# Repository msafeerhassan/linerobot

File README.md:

# Line Following Robot with PID
## Project Overview

Line Following Robot with PID project uses IR Sensors, Microcontroller and Motors to follow a line path on the floor. PID is a type of error-reduction algorithm implemented in such robots to reduce their errors and improve accuracy and precision.
## Project Details
This project is built under Hack Club's Blueprint Program. Custom shape PCB is be used as chassis for the car. PCB covers all components routing alongwith components mounting and soldering. This reduces the wires and improve the project's appearance. Moreover, it reduces the weight due to separate chassis making it more efficient.
N20 Gear Motors with encoders and DRV8833 Motor Driver alongwith QTR 8 Channel IR Sensor Array and ESP32 S3 Devkit are being used. Several capacitors are added to improve the current flow. A Lithium Battery powers this whole project. ESP32 is powered by 5V which is regulated via a Buck Convertor. Motors are powered by 6V and this too is regulated through a 6V 5A Buck Converter.

### PCB:

### Schematic Diagram:

### 3D Model Images:

### Why I made this project?

This was my first ever Hardware Project involving Schematic Design and PCB. I chose this project to strengthen my knowledge and skills of using sensors, microcontrollers etc. I learnt a lot about capacitance, optimum current flow and how sensors work inside. This robot will be used to compete in Line Following Robot competitions like: https://www.dmtsnust.com/nerc/. This project, though difficult but still made me believe that I can build efficient and great Hardware Projects too.

### How it will work
Firstly, battery powers everything and voltage is regulated via Buck Convertors. 
Then the IR Sensor Array gives readings to the ESP32 and based on that, ESP32 alters the speed of motors via Motor Driver.
This allows Robot to stay on line.
When PID is implemented, after this step the ESP32 counts error Value and based on that some manual variables are adjusted that results in increased accuracy and precision.
This loop continues until the robot reaches end of line and then it will stop.

### How to use it?

Firstly, order the PCB from PCB Manufacturing Service. I used JLCPCB: http://jlcpcb.com/ because they offer great and high quality services.
Then order all the components listed in the Bill of Materials.
Solder them all onto the PCB and fully assemble it.
Flash the firmware inside the ESP32. Make sure to adjust variables for better results.
BOOM!!! YOU MADE A COOL LINE FOLLOWING ROBOT.

## Bill of Materials (BOM)

| Item Name                                                   | Quantity | Link                                                                                                                              | Cost   |
|:------------------------------------------------------------|---------:|:----------------------------------------------------------------------------------------------------------------------------------|:-------|
| ESP32-DevKit-S3-WROOM1                                      |        1 | [Link](https://epro.pk/product/pre-soldered-esp32-s3-wroom-1-development-board-2-4g-wifi-bt-module/)                              | $6.41  |
| DRV8833 Motor Driver                                        |        1 | [Link](https://epro.pk/product/tb6612-drv8833-dual-motor-driver-module-1a-h-bridge-for-arduino-robotics/)                         | $1.98  |
| 6V N20 Gear Motor with encoder, wheel and mounting brackets |        2 | [Link](https://www.aliexpress.com/item/1005004110888400.html)                                                                     | $16.35 |
| 5A Buck DC-DC Converter 7.4V to 6V                          |        1 | [Link](https://www.aliexpress.com/item/4000496873234.html)                                                                        | $4.84  |
| 7.4V to 5V 1A DC-DC Fixed Buck Convertor (for ESP32)        |        1 | [Link](https://www.aliexpress.com/item/1005006005553178.html)                                                                     | $1.86  |
| 470 µF, 16 V aluminium electrolytic capacitor               |        2 | [Link](https://epro.pk/product/470uf-16v-aluminum-electrolytic-capacitor/)                                                        | $0.11  |
| 220 µF, 10 V aluminium electrolytic capacitor               |        1 | We'll buy it ourself                                                                                                              | $0.00  |
| 100 nF Ceramic Capacitor                                    |        2 | [Link](https://epro.pk/product/0-1uf-100nf-100000pf-104-ceramic-capacitor-in-pakistan/)                                           | $0.02  |
| 8 Channel IR Sensor Array                                   |        1 | [Link](https://epro.pk/product/qtr-8rc-line-following-reflectance-ir-sensor-8-channel-line-following-line-tracking-array-module/) | $2.30  |
| LiPo Battery 7.4V 1500mAH                                   |        1 | [Link](https://epro.pk/product/zop-power-7-4v-1500mah-li-po-rechargeable-battery-pack/)                                           | $10.04 |
| PCB                                                         |        1 | No Link:(                                                                                                                         | $36.25 |
| Push Switch Button                                          |        1 | [Link](https://epro.pk/product/slider-on-off-switch/)                                                                             | $0.05  |
| TAXES:(                                                     |        0 | No Link:(                                                                                                                         | $16.14 |
| Total Cost                                                  |        0 |                                                                                                                                   | $96.35 |

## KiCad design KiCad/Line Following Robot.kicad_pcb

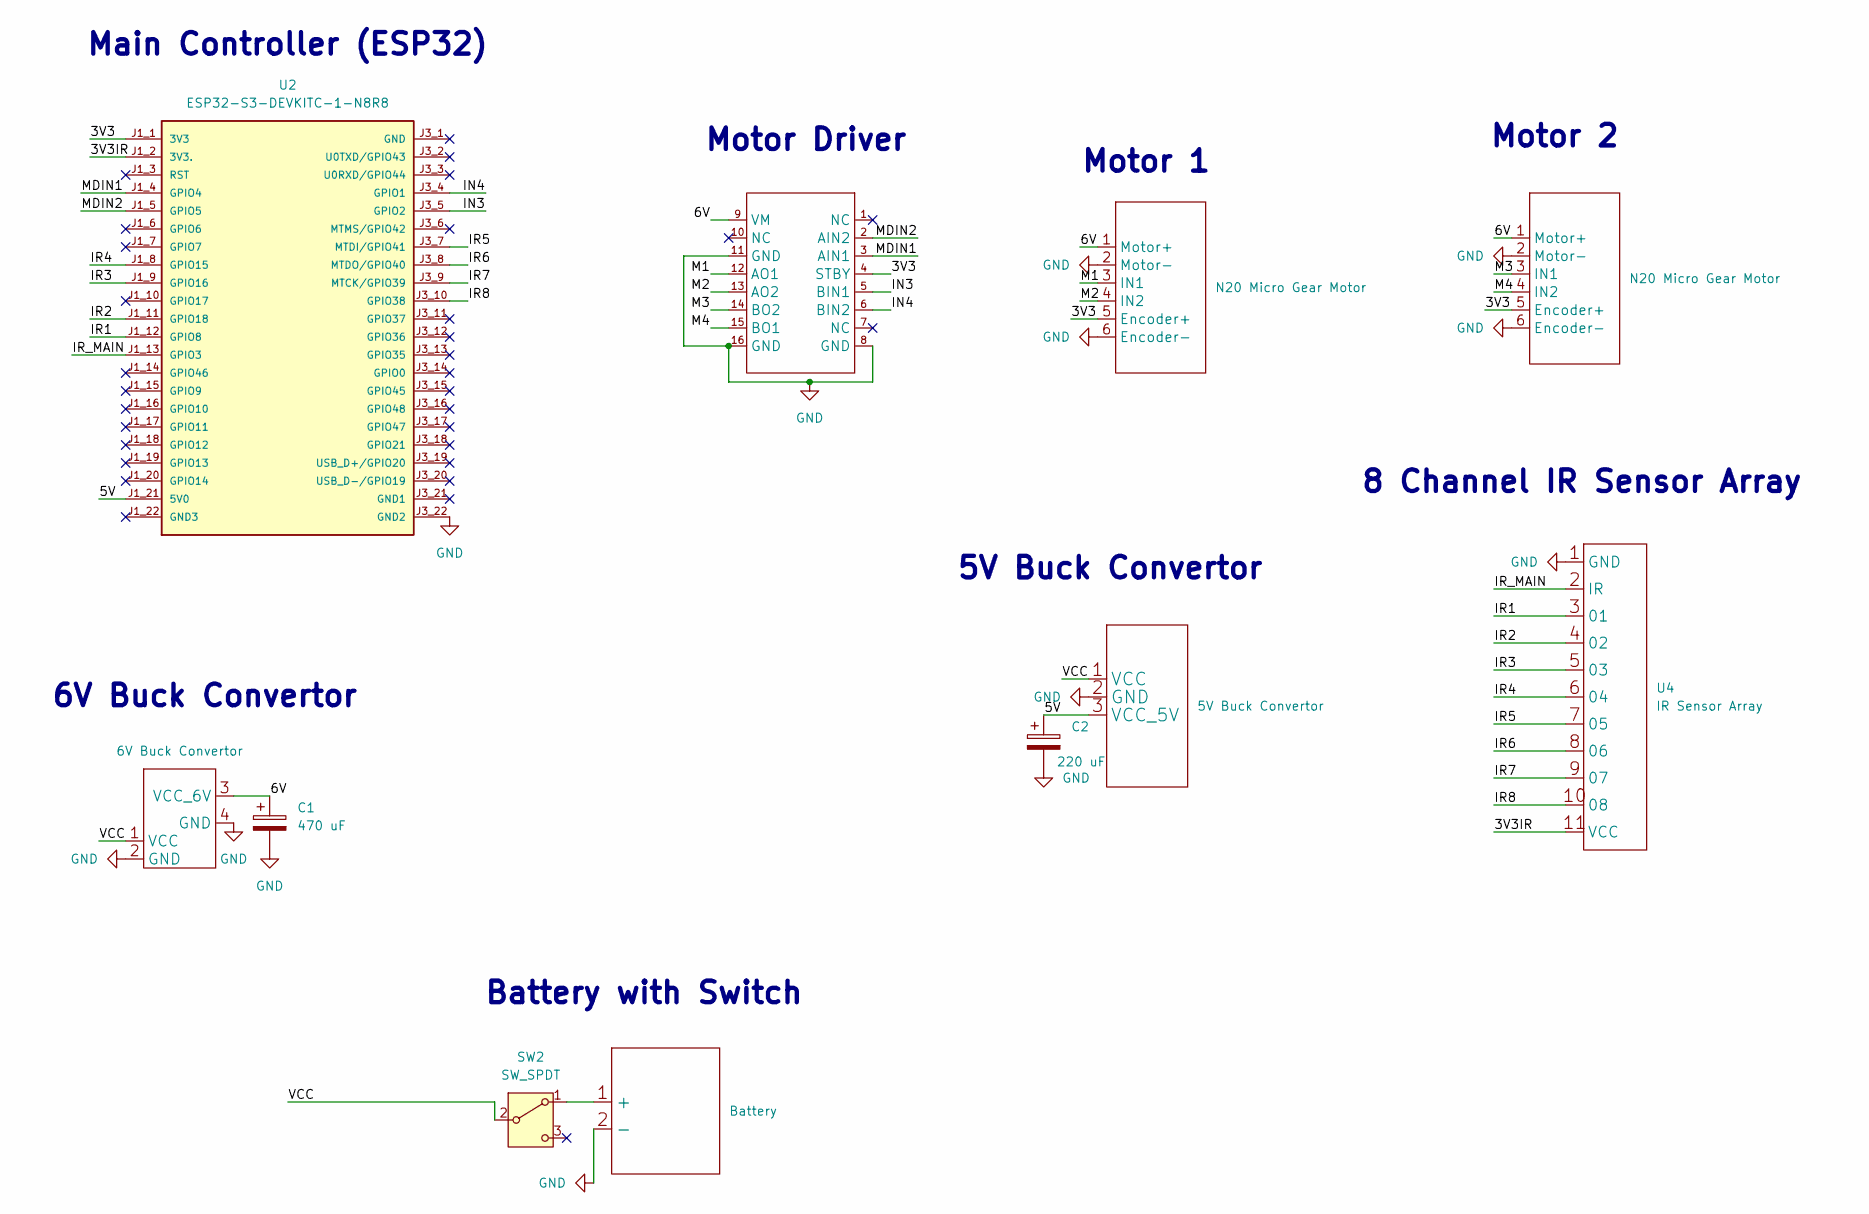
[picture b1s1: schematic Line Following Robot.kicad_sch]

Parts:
A1, A2: N20 Micro Gear Motor; Motor
C1: 470 uF; Capacitor
C2: 220 uF; Capacitor
SW2: SW_SPDT; SW_Slide-03_Wuerth-WS-SLTV_10x2.5x6.4_P2.54mm
U1: 5V Buck Convertor
U2: ESP32-S3-DEVKITC-1-N8R8
U3: 6V Buck Convertor; 6V New Buck Convertor
U4: IR Sensor Array
U6: PinHeader_1x08_P2.54mm_Vertical
U7: Battery

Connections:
/3V3: A1.5 (Encoder+), A2.5 (Encoder+), U2.J1_1 (3V3), U6.4 (STBY)
/3V3IR: U2.J1_2 (3V3.), U4.11 (VCC)
/5V: C2.1, U1.3 (VCC_5V), U2.J1_21 (5V0)
/6V: A1.1 (Motor+), A2.1 (Motor+), C1.1, U3.3 (VCC_6V), U6.9 (VM)
/IN3: U2.J3_5 (GPIO2), U6.5 (BIN1)
/IN4: U2.J3_4 (GPIO1), U6.6 (BIN2)
/IR1: U2.J1_12 (GPIO8), U4.3 (01)
/IR2: U2.J1_11 (GPIO18), U4.4 (02)
/IR3: U2.J1_9 (GPIO16), U4.5 (03)
/IR4: U2.J1_8 (GPIO15), U4.6 (04)
/IR5: U2.J3_7 (MTDI/GPIO41), U4.7 (05)
/IR6: U2.J3_8 (MTDO/GPIO40), U4.8 (06)
/IR7: U2.J3_9 (MTCK/GPIO39), U4.9 (07)
/IR8: U2.J3_10 (GPIO38), U4.10 (08)
/IR_MAIN: U2.J1_13 (GPIO3), U4.2 (IR)
/M1: A2.3 (IN1), U6.12 (AO1)
/M2: A2.4 (IN2), U6.13 (AO2)
/M3: A1.3 (IN1), U6.14 (BO2)
/M4: A1.4 (IN2), U6.15 (BO1)
/MDIN1: U2.J1_4 (GPIO4), U6.3 (AIN1)
/MDIN2: U2.J1_5 (GPIO5), U6.2 (AIN2)
/VCC: SW2.2 (B), U1.1 (VCC), U3.1 (VCC)
GND: A1.2 (Motor-), A1.6 (Encoder-), A2.2 (Motor-), A2.6 (Encoder-), C1.2, C2.2, U1.2 (GND), U2.J3_22 (GND2), U3.2 (GND), U3.4 (GND), U4.1 (GND), U6.8 (GND), U6.11 (GND), U6.16 (GND), U7.2 (-)
unnamed: SW2.1 (A), U7.1 (+)

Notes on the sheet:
6V Buck Convertor
Motor Driver
Motor 2
5V Buck Convertor
8 Channel IR Sensor Array
Main Controller (ESP32)
Battery with Switch
Motor 1

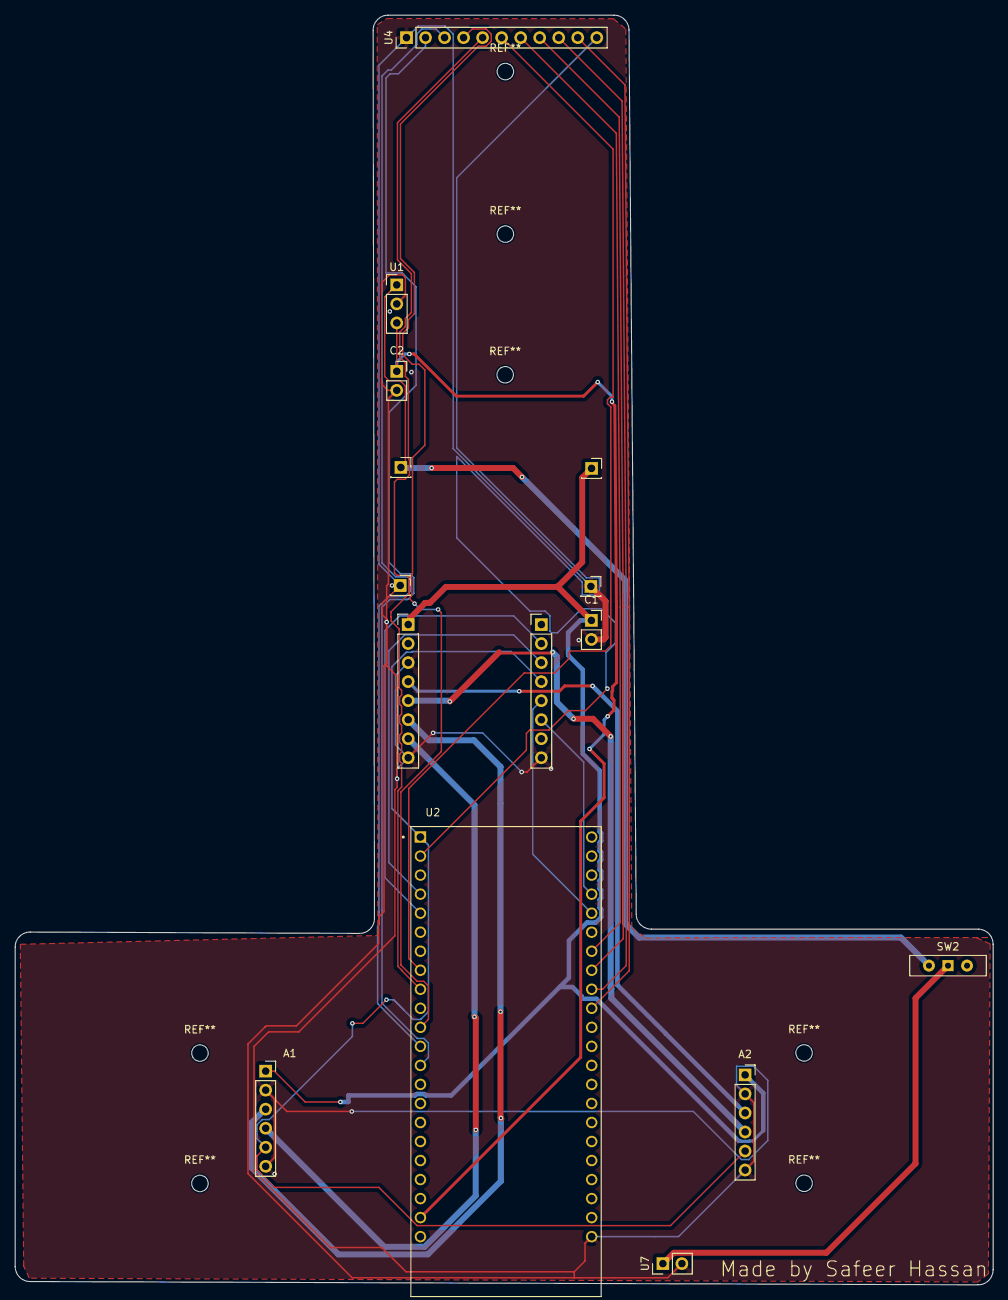
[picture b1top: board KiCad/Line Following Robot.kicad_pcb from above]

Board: 2 copper layers, 130.5 x 169.5 mm, 11 parts (0 on the bottom side), 24 nets.

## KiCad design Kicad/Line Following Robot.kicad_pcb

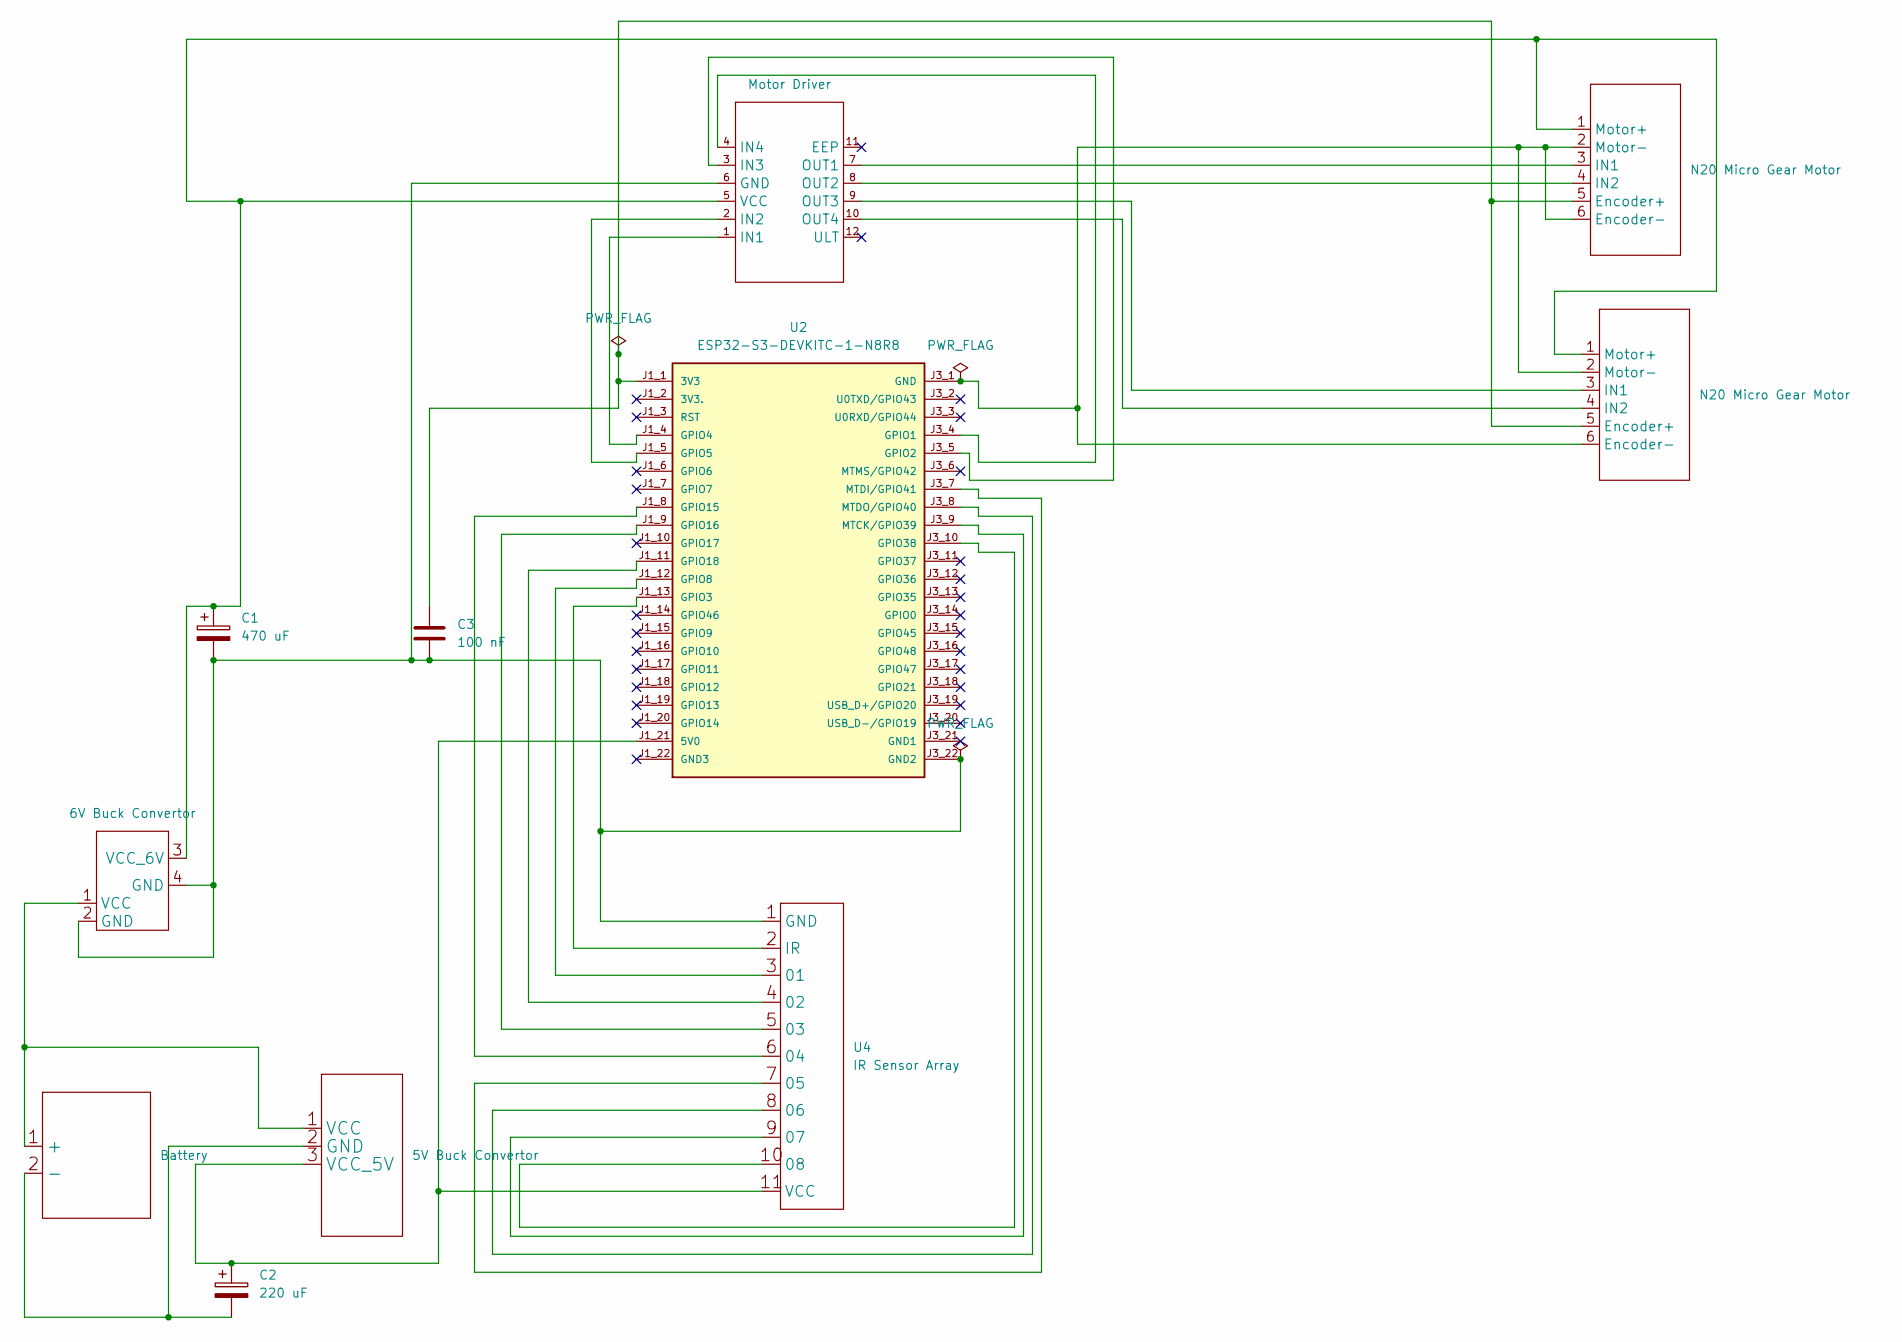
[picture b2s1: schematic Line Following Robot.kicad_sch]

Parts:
A1, A2: N20 Micro Gear Motor; Motor
C1: 470 uF; Capacitor
C2: 220 uF; Capacitor
C3: 100 nF; Capacitor
U1: 5V Buck Convertor
U2: ESP32-S3-DEVKITC-1-N8R8
U3: 6V Buck Convertor; 6V New Buck Convertor
U4: IR Sensor Array
U5: Motor Driver
U7: Battery

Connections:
unnamed: A1.5 (Encoder+), A2.5 (Encoder+), C3.1, U2.J1_1 (3V3)
unnamed: A1.2 (Motor-), A1.6 (Encoder-), A2.2 (Motor-), A2.6 (Encoder-), U2.J3_1 (GND)
unnamed: A1.3 (IN1), U5.9 (OUT3)
unnamed: A1.4 (IN2), U5.10 (OUT4)
unnamed: A1.1 (Motor+), A2.1 (Motor+), C1.1, U3.3 (VCC_6V), U5.5 (VCC)
unnamed: A2.3 (IN1), U5.7 (OUT1)
unnamed: A2.4 (IN2), U5.8 (OUT2)
unnamed: C2.2, U1.2 (GND), U7.2 (-)
unnamed: U1.1 (VCC), U3.1 (VCC), U7.1 (+)
unnamed: C2.1, U1.3 (VCC_5V), U2.J1_21 (5V0), U4.11 (VCC)
unnamed: C1.2, C3.2, U2.J3_22 (GND2), U3.2 (GND), U3.4 (GND), U4.1 (GND), U5.6 (GND)
unnamed: U2.J3_4 (GPIO1), U5.4 (IN4)
unnamed: U2.J3_5 (GPIO2), U5.3 (IN3)
unnamed: U2.J1_13 (GPIO3), U4.2 (IR)
unnamed: U2.J1_4 (GPIO4), U5.1 (IN1)
unnamed: U2.J1_5 (GPIO5), U5.2 (IN2)
unnamed: U2.J1_12 (GPIO8), U4.3 (01)
unnamed: U2.J1_8 (GPIO15), U4.6 (04)
unnamed: U2.J1_9 (GPIO16), U4.5 (03)
unnamed: U2.J1_11 (GPIO18), U4.4 (02)
unnamed: U2.J3_10 (GPIO38), U4.10 (08)
unnamed: U2.J3_9 (MTCK/GPIO39), U4.9 (07)
unnamed: U2.J3_7 (MTDI/GPIO41), U4.7 (05)
unnamed: U2.J3_8 (MTDO/GPIO40), U4.8 (06)

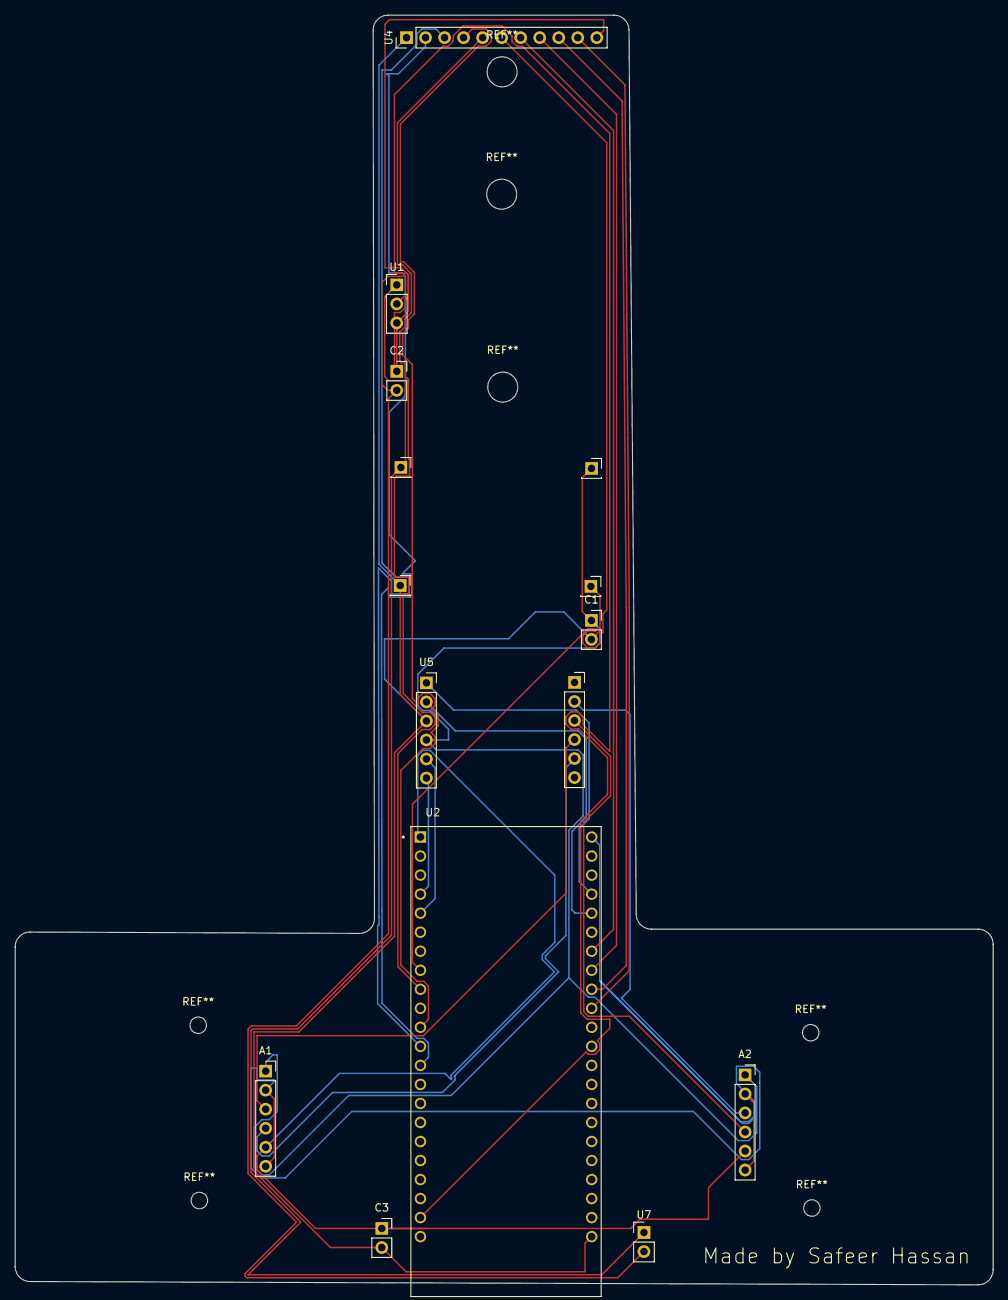
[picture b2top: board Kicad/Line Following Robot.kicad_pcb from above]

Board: 2 copper layers, 130.5 x 169.5 mm, 11 parts (0 on the bottom side), 24 nets.

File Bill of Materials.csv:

,,,,,,,,,,
,,,,Item Name,Quantity,Sourcing Link,Cost,Shipping Cost,,
,,,,ESP32 C6 DevKitM1,1,https://www.aliexpress.com/item/1005006902472832.html,$11.67 ,$3.72 ,,
,,,,DRV8833 Dual Motor Driver 1.5A,1,https://www.aliexpress.com/item/1005009787121900.html,$1.33 ,$0 ,,
,,,,6V N20 Micro Gear Motor with Encoder and Wheel,2,https://www.aliexpress.com/item/1005004110888400.html,$12.34 ,$6.15 ,,
,,,,Li-ion Battery 7.4V 2500mAH with Charger,1,https://www.aliexpress.com/item/1005009278092026.html,$21.44 ,$0 ,,
,,,,Caster Ball 22mm height,1,https://www.aliexpress.com/item/1005007433451446.html,$2.60 ,$0 ,,
,,,,5A Buck DC-DC Converter 7.4V to 6V,1,https://www.aliexpress.com/item/4000497173017.html,$5.81 ,$0 ,,
,,,,7.4V to 5V 1A DC-DC Fixed Buck Convertor (for ESP32),1,https://www.aliexpress.com/item/1005008119609403.html,$0.37 ,$3.50 ,,
,,,,"470 µF, 16 V aluminium electrolytic capacitor",10 (min. order),https://www.aliexpress.com/item/1005009114608575.html,$2.81 ,$0 ,,
,,,,"220 µF, 10 V aluminium electrolytic capacitor",10 (min. order),https://www.aliexpress.com/item/1005009114608575.html,$2.35 ,$0 ,,
,,,,"100 nF, 50 V Ceramic Capacitor",100 (min. order),https://www.aliexpress.com/item/1005007929336683.html,$0.99 ,$0 ,,
,,,,On/Off Power Switch,1,We already have this,ZERO,ZERO,,
,,,,8 Channel IR Sensor Array,1,https://www.aliexpress.com/item/1005009116199722.html,$0.86 ,$3.05 ,,
,,,,PCB,1,No Link:(,$12.40 ,$18.89 ,,
,,,,TAXES,A LOTTTT,No Link:(,$55.29 ,Not Applicable,,
,,,,Total,,$165.57 ,,,,
,,,,,,,,,,
,,,,,,,,,,
,,,,,,,,,,
,,,,,,,,,,
,,,,,,,,,,
,,,,,,,,,,
,,,,,,,,,,
,,,,,,,,,,
,,,,,,,,,,
,,,,,,,,,,
,,,,,,,,,,
,,,,,,,,,,
,,,,,,,,,,
,,,,,,,,,,
,,,,,,,,,,

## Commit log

2025-12-04 kicad files upload
2025-12-04 uploaded BoM
2025-12-04 BoM in excel and csv format
2025-12-04 screenshots uploaded
2025-12-07 Added readme for Line Following Robot
2025-12-17 changes committed
2026-01-04 updated BoM with lower cost :)
2026-01-09 updated CAD Files
2026-01-09 updated KiCad files
2026-01-09 Revise README with updated project specifications
    Updated project details and specifications for the Line Following Robot. Changed ESP32 Devkit to ESP32 S3 and added PCB images.
2026-01-20 Update competition link in readme
2026-02-09 Enhance README with new images and project details
    Updated images and descriptions in the README for PCB, schematic diagrams, and 3D models.
2026-02-09 Whole Project Recommit - Fixed Schematic, PCB, Gerber, 3D Model
2026-02-10 fixed pcb
2026-02-14 added step file
2026-02-15 Enhance README with project details and instructions
    Added sections for PCB, schematic diagrams, 3D model images, project motivation, usage instructions, and bill of materials.
2026-02-15 Removed everything bcz got messed up
2026-02-15 Add all files again....
2026-03-04 added f3z file
2026-03-07 fixed everything
2026-03-07 Rename 'TAXES & Logistics' to 'TAXES'
2026-03-08 fixed pcb and schematic
2026-03-14 fixed footprint
2026-03-18 updated BoM
2026-03-18 updated BoM and readme
